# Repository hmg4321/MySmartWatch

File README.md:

WatchMe

My Personal SmartWatch

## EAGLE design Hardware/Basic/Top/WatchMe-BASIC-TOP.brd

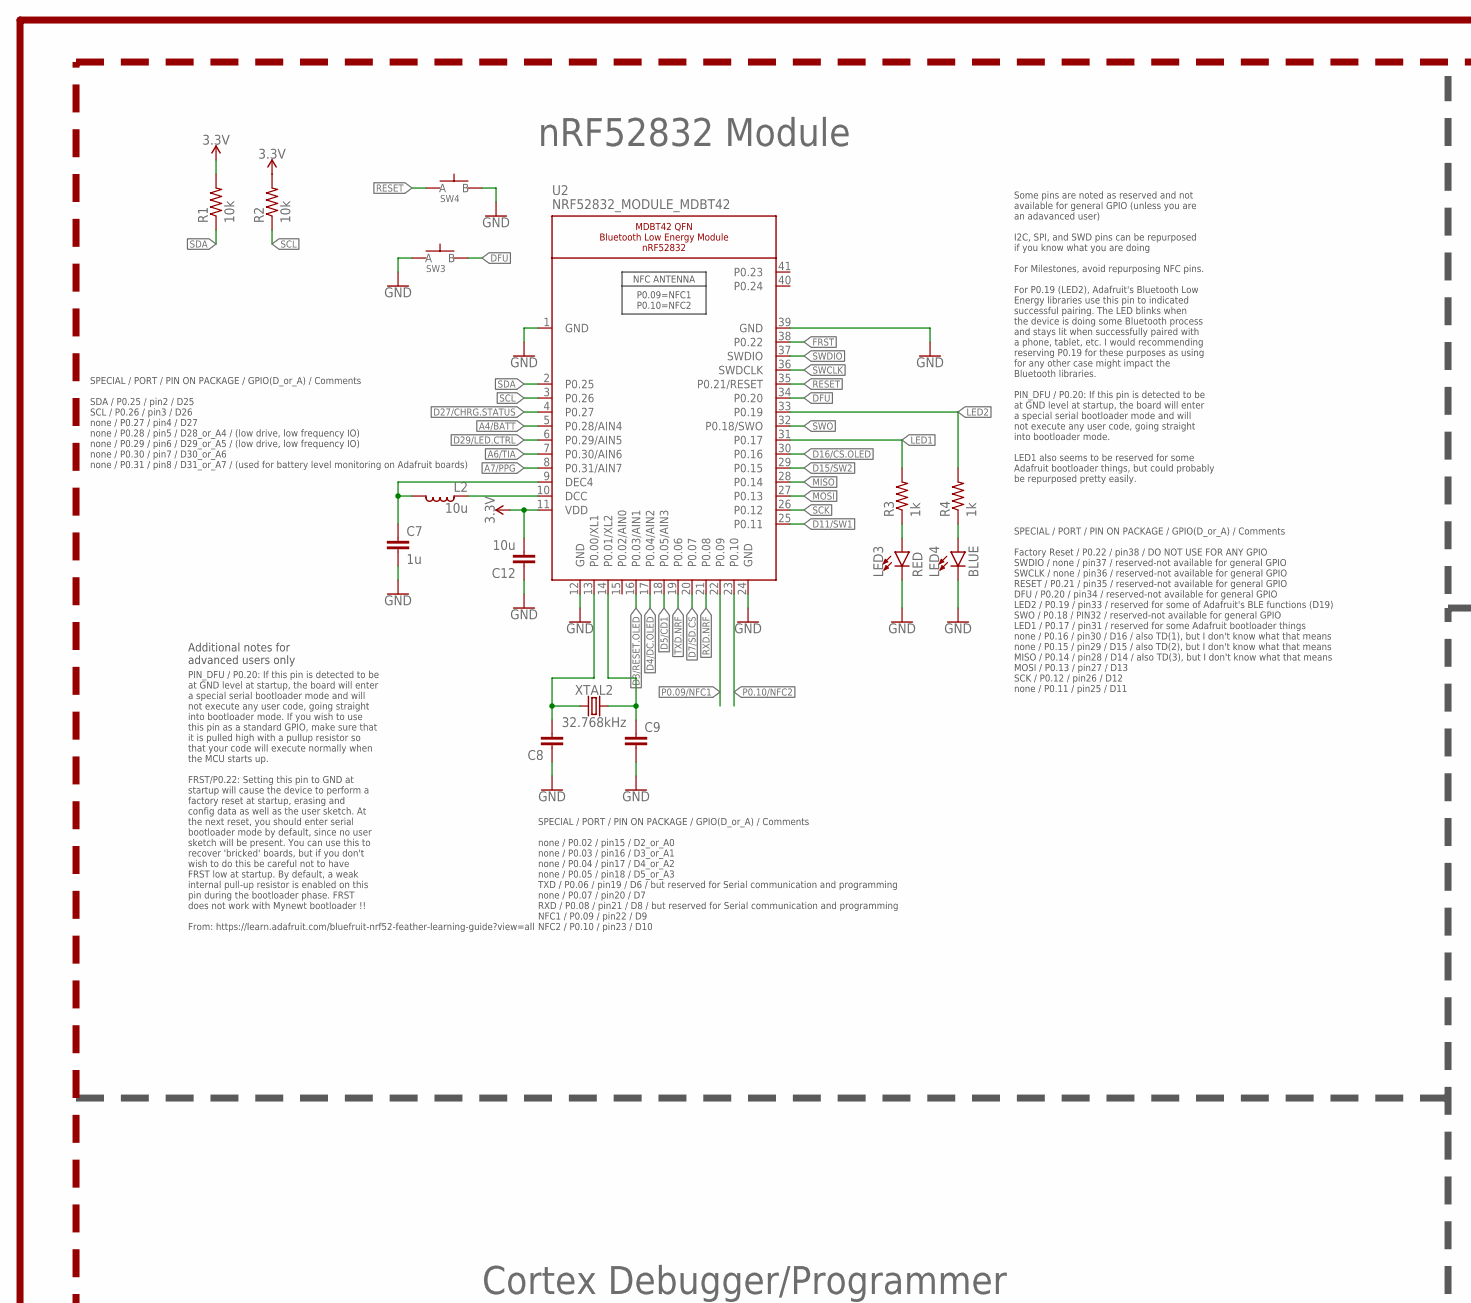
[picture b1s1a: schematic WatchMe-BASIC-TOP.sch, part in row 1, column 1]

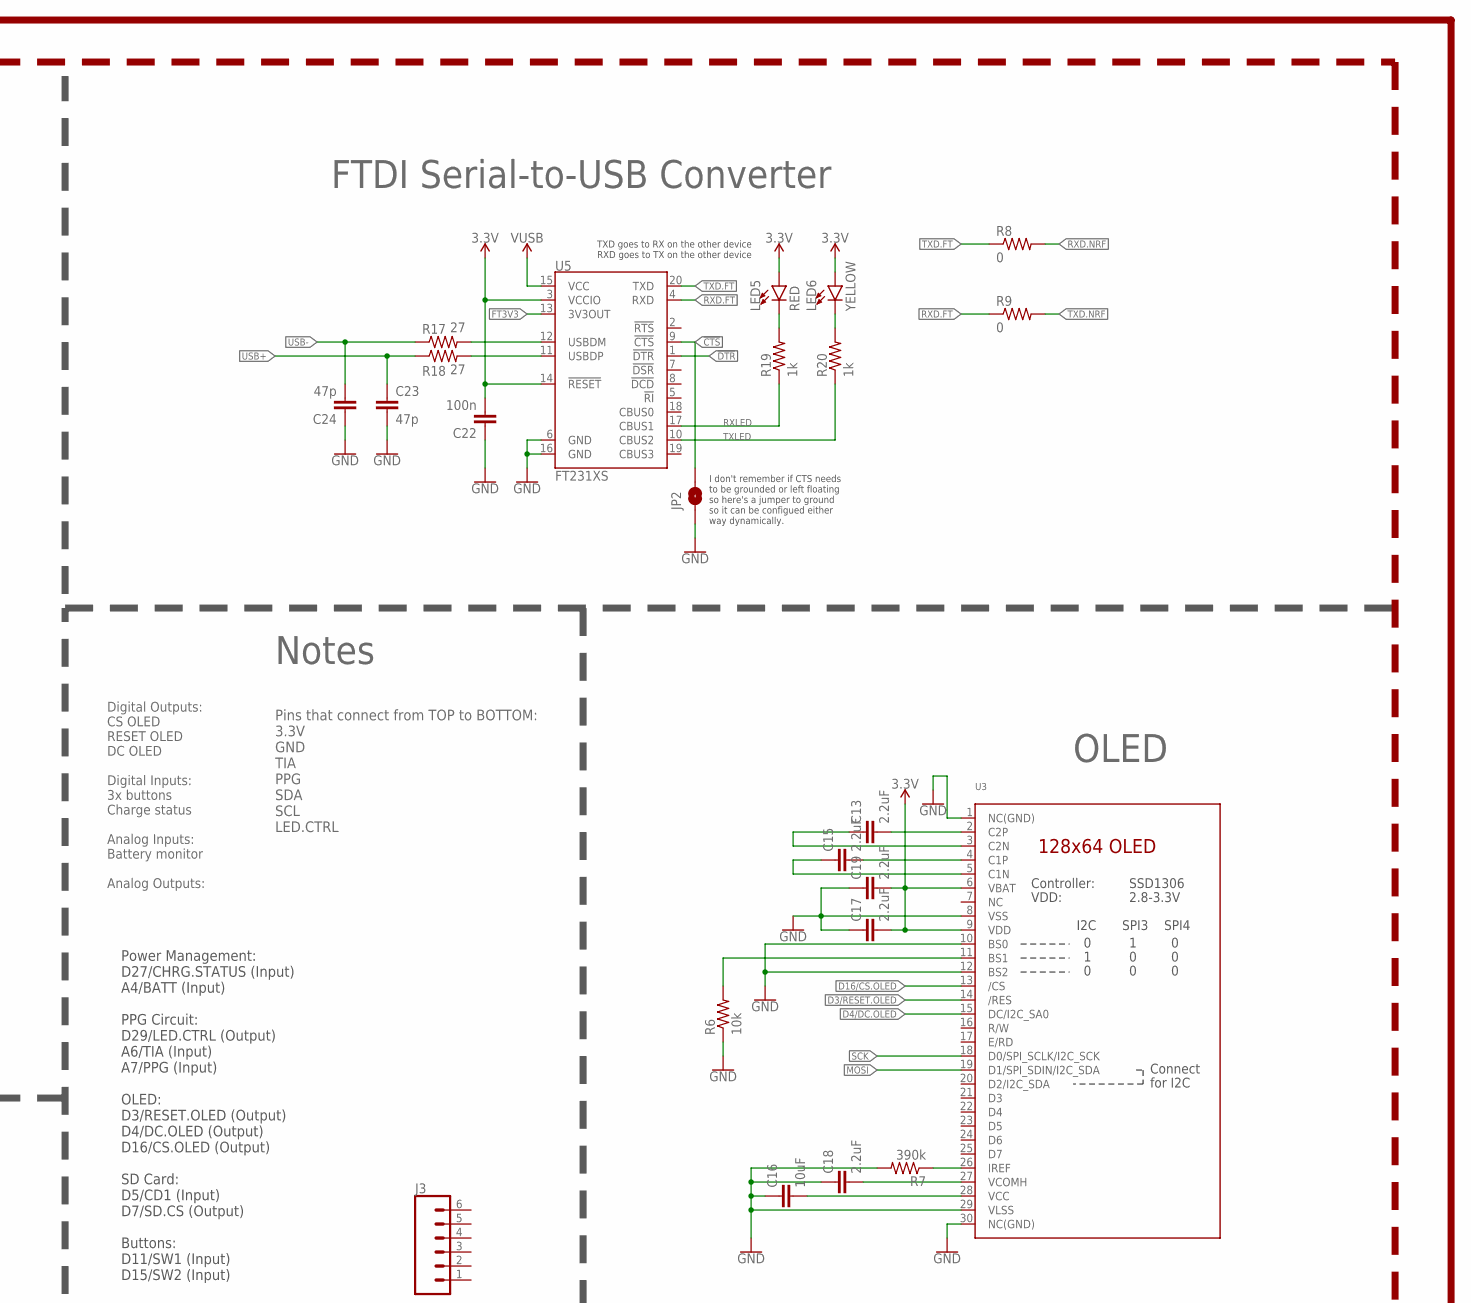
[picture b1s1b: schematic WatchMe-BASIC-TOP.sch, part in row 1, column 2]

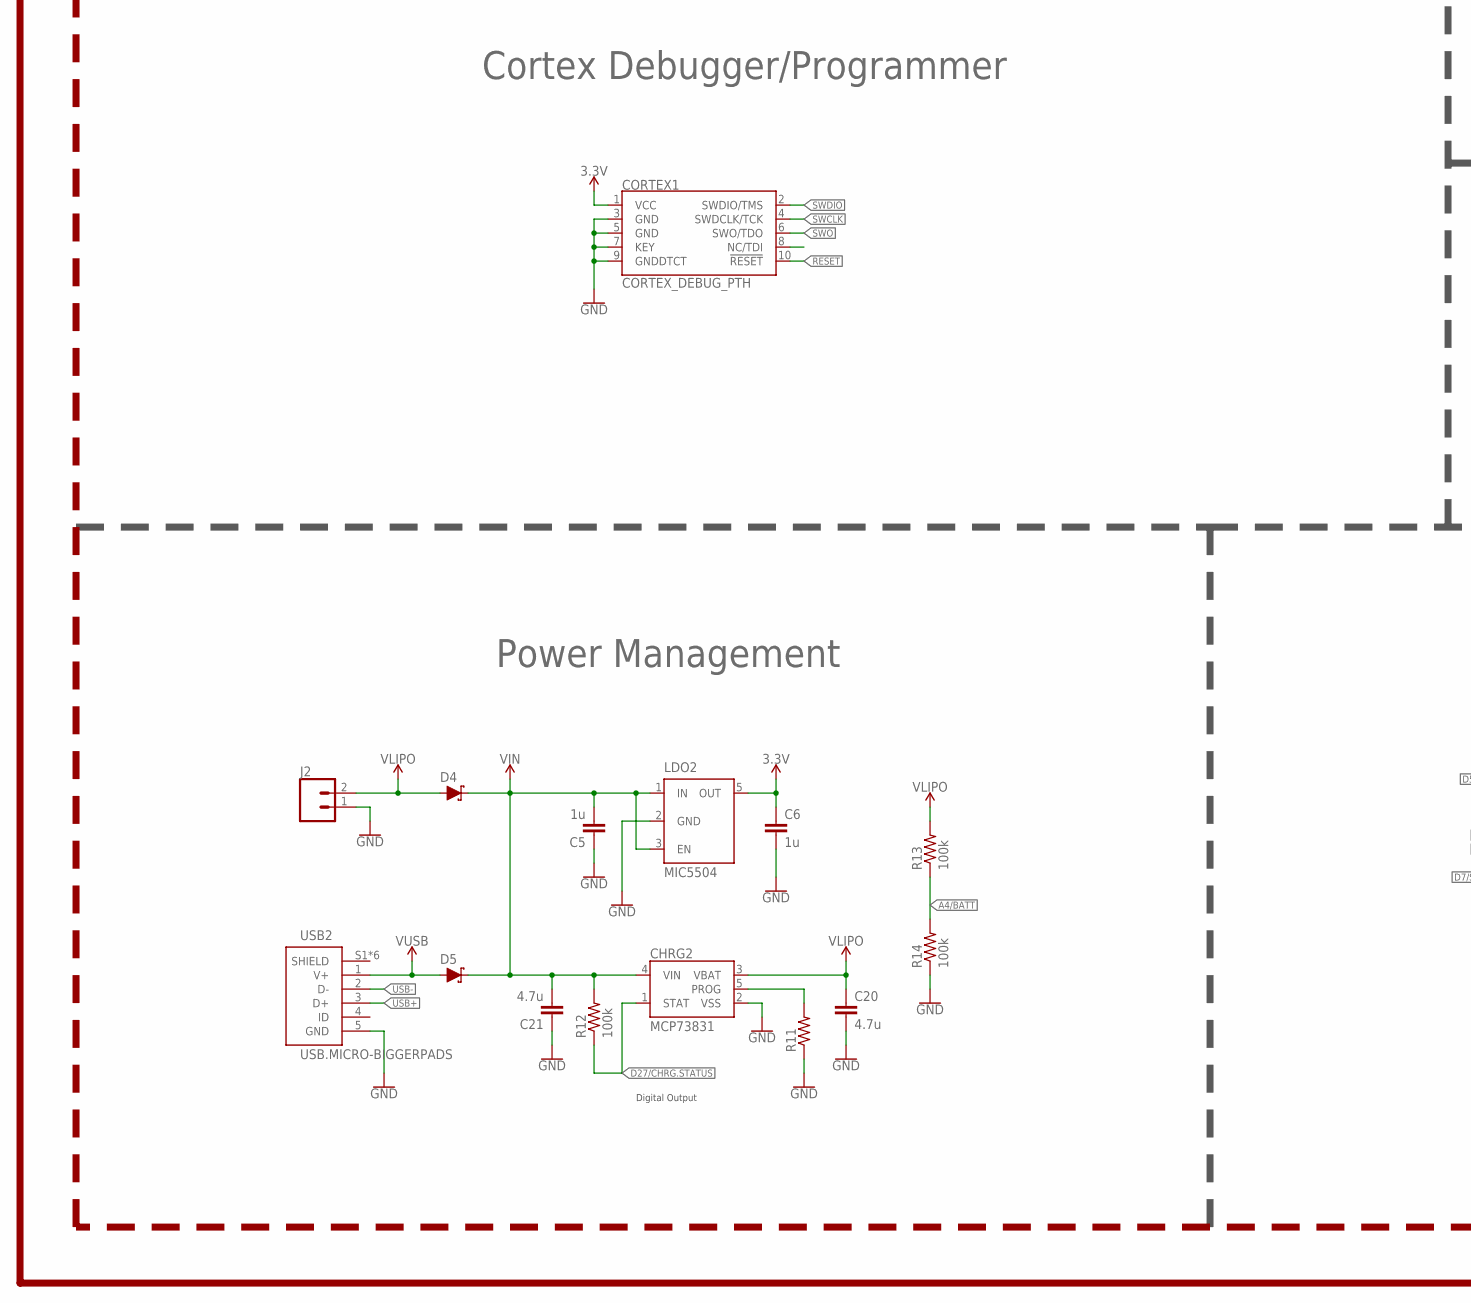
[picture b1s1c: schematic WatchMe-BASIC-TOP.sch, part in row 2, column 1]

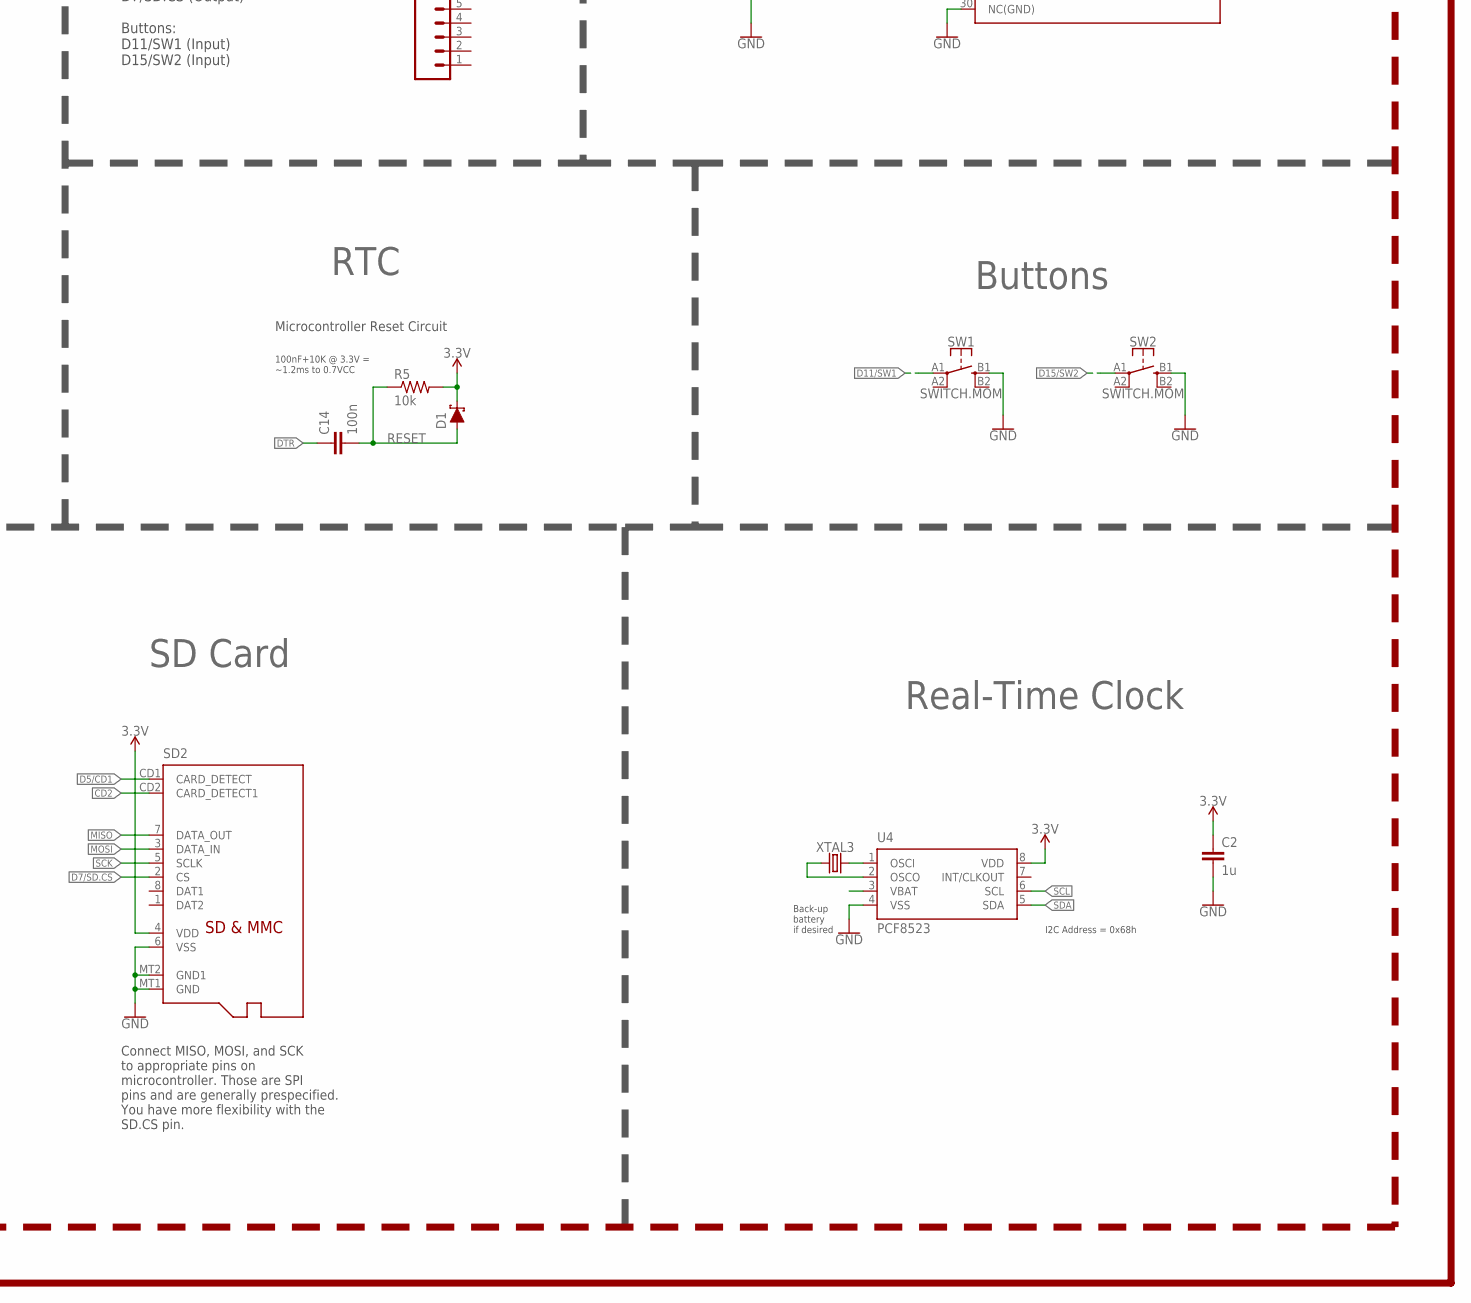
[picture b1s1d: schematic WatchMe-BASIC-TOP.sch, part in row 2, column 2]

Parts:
C2, C5, C6, C7: 1u; C0603
C8, C9: CAPACITOR0603; C0603
C12: 10u; C0805
C13, C15, C17, C18, C19: 2.2uF; C0402
C14, C22: 100n; C0603
C16: 10uF; C0603
C20, C21: 4.7u; C0603
C23, C24: 47p; C0603
CHRG2: MCP73831; SOT23-5
CORTEX1: CORTEX_DEBUG_PTH; 2X5-PTH-1.27MM
D1, D4, D5: SCHOTTKY-USC; USC
J2: CONN_02; 1X02
J3: CONN_061.27MM; 1X06_1.27MM
JP2: JUMPER-SMT_2_NO_SILK; SMT-JUMPER_2_NO_SILK
L2: 10u; L0603
LDO2: MIC5504; SOT23-5
LED3, LED5: RED; LED-0603
LED4: BLUE; LED-0603
LED6: YELLOW; LED-0603
R1, R2, R5, R6: 10k; R0603
R3, R4, R19, R20: 1k; R0603
R7: 390k; R0603
R8, R9: 0; R0603
R11: RESISTOR0603; R0603
R12, R13, R14: 100k; R0603
R17, R18: 27; R0603
SD2: MICROSD
SW1, SW2: SWITCH.MOM; TACTILE_SWITCH_SMD_6.2MM_TALL
SW3, SW4: SPST-PTS830GG140-COPY.1-3; BUTTON-GULLWING
U2: NRF52832_MODULE_MDBT42; BLE_MODULE_RAYTAC_MDBT42
U3: DISP_OLED_UG-2864HSWEG01-NO-WRAPAROUND; UG-2864HSWEG01_0.96IN_NO-WRAPAROUND
U4: PCF8523; SO8; DIGIKEY 568-5306-1-ND
U5: FT231XS; SSOP20_L
USB2: USB.MICRO-BIGGERPADS; USB-MICRO-01.BIGGERPADS
XTAL2: 32.768kHz; 2-SMD.NOLEAD.2.0MMTO1.2MM
XTAL3: 32.7680kHz; 2-SMD.NOLEAD.2.0MMTO1.2MM

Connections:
3.3V: C2.1, C6.1, C12.2, C17.2, C19.2, C22.2, CORTEX1.1 (VCC), D1.- (C), LDO2.5 (OUT), LED5.A, LED6.A, R1.2, R2.2, R5.2, SD2.4 (VDD), U2.11 (VDD), U3.6 (VBAT), U3.9 (VDD), U4.8 (VDD), U5.3 (VCCIO), U5.14 (!RESET)
!CTS: JP2.2, U5.9 (!CTS)
!DTR: U5.1 (!DTR)
A4/BATT: R13.1, R14.2, U2.5 (P0.28/AIN4)
A6/TIA: U2.7 (P0.30/AIN6)
A7/PPG: U2.8 (P0.31/AIN7)
CD2: SD2.CD2 (CARD_DETECT1)
D3/RESET.OLED: U2.16 (P0.03/AIN1), U3.14 (/RES)
D4/DC.OLED: U2.17 (P0.04/AIN2), U3.15 (DC/I2C_SA0)
D5/CD1: SD2.CD1 (CARD_DETECT), U2.18 (P0.05/AIN3)
D7/SD.CS: SD2.2 (CS), U2.20 (P0.07)
D11/SW1: SW1.A1 (1), U2.25 (P0.11)
D15/SW2: SW2.A1 (1), U2.29 (P0.15)
D16/CS.OLED: U2.30 (P0.16), U3.13 (/CS)
D27/CHRG.STATUS: CHRG2.1 (STAT), R12.1, U2.4 (P0.27)
D29/LED.CTRL: U2.6 (P0.29/AIN5)
DFU: SW3.3 (B), U2.34 (P0.20)
DTR: C14.1
FRST: U2.38 (P0.22)
FT3V3: U5.13 (3V3OUT)
GND: C2.2, C5.1, C6.2, C7.2, C8.1, C9.2, C12.1, C16.1, C17.1, C18.1, C19.1, C20.2, C21.1, C22.1, C23.2, C24.1, CHRG2.2 (VSS), CORTEX1.3 (GND), CORTEX1.5 (GND), CORTEX1.7 (KEY), CORTEX1.9 (GNDDTCT), J2.1, JP2.1, LDO2.2 (GND), LED3.C, LED4.C, R6.1, R7.2, R11.1, R14.1, SD2.6 (VSS), SD2.MT1 (GND), SD2.MT2 (GND1), SW1.B1 (3), SW2.B1 (3), SW3.1 (A), SW4.3 (B), U2.1 (GND), U2.12 (GND), U2.24 (GND), U2.39 (GND), U3.1 (NC(GND)), U3.8 (VSS), U3.10 (BS0), U3.12 (BS2), U3.29 (VLSS), U3.30 (NC(GND)), U4.4 (VSS), U5.6 (GND), U5.16 (GND), USB2.5 (GND)
LED1: R3.2, U2.31 (P0.17)
LED2: R4.2, U2.33 (P0.19)
MISO: SD2.7 (DATA_OUT), U2.28 (P0.14)
MOSI: SD2.3 (DATA_IN), U2.27 (P0.13), U3.19 (D1/SPI_SDIN/I2C_SDA)
unnamed: R6.2, U3.11 (BS1)
unnamed: R7.1, U3.26 (IREF)
unnamed: C13.2, U3.2 (C2P)
unnamed: C8.2, U2.13 (P0.00/XL1), XTAL2.P$1 (1)
unnamed: C13.1, U3.3 (C2N)
unnamed: C9.1, U2.14 (P0.01/XL2), XTAL2.P$2 (2)
unnamed: C15.2, U3.4 (C1P)
unnamed: C15.1, U3.5 (C1N)
unnamed: LED3.A, R3.1
unnamed: LED4.A, R4.1
unnamed: L2.1, U2.10 (DCC)
unnamed: C7.1, L2.2, U2.9 (DEC4)
unnamed: C16.2, U3.28 (VCC)
unnamed: C18.2, U3.27 (VCOMH)
unnamed: CHRG2.5 (PROG), R11.2
unnamed: U4.2 (OSCO), XTAL3.P$1 (1)
unnamed: U4.1 (OSCI), XTAL3.P$2 (2)
unnamed: R17.2, U5.12 (USBDM)
unnamed: R18.2, U5.11 (USBDP)
unnamed: LED5.C, R19.2
unnamed: LED6.C, R20.2
P0.09/NFC1: U2.22 (P0.09)
P0.10/NFC2: U2.23 (P0.10)
RESET: C14.2, CORTEX1.10 (!RESET), D1.+ (A), R5.1, SW4.1 (A), U2.35 (P0.21/RESET)
RXD.FT: R9.1, U5.4 (RXD)
RXD.NRF: R8.2, U2.21 (P0.08)
RXLED: R19.1, U5.17 (CBUS1)
SCK: SD2.5 (SCLK), U2.26 (P0.12), U3.18 (D0/SPI_SCLK/I2C_SCK)
SCL: R2.1, U2.3 (P0.26), U4.6 (SCL)
SDA: R1.1, U2.2 (P0.25), U4.5 (SDA)
SWCLK: CORTEX1.4 (SWDCLK/TCK), U2.36 (SWDCLK)
SWDIO: CORTEX1.2 (SWDIO/TMS), U2.37 (SWDIO)
SWO: CORTEX1.6 (SWO/TDO), U2.32 (P0.18/SWO)
TXD.FT: R8.1, U5.20 (TXD)
TXD.NRF: R9.2, U2.19 (P0.06)
TXLED: R20.1, U5.10 (CBUS2)
USB+: C23.1, R18.1, USB2.3 (D+)
USB-: C24.2, R17.1, USB2.2 (D-)
VBATT: U4.3 (VBAT)
VIN: C5.2, C21.2, CHRG2.4 (VIN), D4.- (C), D5.- (C), LDO2.1 (IN), LDO2.3 (EN), R12.2
VLIPO: C20.1, CHRG2.3 (VBAT), D4.+ (A), J2.2, R13.2
V_USB: D5.+ (A), U5.15 (VCC), USB2.1 (V+)

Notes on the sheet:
Microcontroller Reset Circuit
100nF+10K @ 3.3V = ~1.2ms to 0.7VCC
SPECIAL / PORT / PIN ON PACKAGE / GPIO(D_or_A) / Comments SDA / P0.25 / pin2 / D25 SCL / P0.26 / pin3 / D26 none / P0.27 / pin4 / D27 none / P0.28 / pin5 / D28_or_A4 / (low drive, low frequency IO) none / P0.29 / pin6 / D29_or_A5 / (low drive, low frequency IO) none / P0.30 / pin7 / D30_or_A6 none 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
SPECIAL / PORT / PIN ON PACKAGE / GPIO(D_or_A) / Comments none / P0.02 / pin15 / D2_or_A0 none / P0.03 / pin16 / D3_or_A1 none / P0.04 / pin17 / D4_or_A2 none / P0.05 / pin18 / D5_or_A3 TXD / P0.06 / pin19 / D6 / but reserved for Serial communication and programming none / P0.07 / pin20 / D7 RXD / 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
SPECIAL / PORT / PIN ON PACKAGE / GPIO(D_or_A) / Comments Factory Reset / P0.22 / pin38 / DO NOT USE FOR ANY GPIO SWDIO / none / pin37 / reserved-not available for general GPIO SWCLK / none / pin36 / reserved-not available for general GPIO RESET / P0.21 / pin35 / reserved-not available for general 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
Some pins are noted as reserved and not available for general GPIO (unless you are an adavanced user) I2C, SPI, and SWD pins can be repurposed if you know what you are doing For Milestones, avoid repurposing NFC pins. For P0.19 (LED2), Adafruit's Bluetooth Low Energy libraries use this pin to indic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
PIN_DFU / P0.20: If this pin is detected to be at GND level at startup, the board will enter a special serial bootloader mode and will not execute any user code, going straight into bootloader mode. If you wish to use this pin as a standard GPIO, make sure that it is pulled high with a pullup resis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
Additional notes for advanced users only
Connect MISO, MOSI, and SCK to appropriate pins on microcontroller. Those are SPI pins and are generally prespecified. You have more flexibility with the SD.CS pin.
I2C Address = 0x68h
Back-up battery if desired
nRF52832 Module
Power Management
SD Card
Buttons
Real-Time Clock
OLED
Cortex Debugger/Programmer
RTC
TXD goes to RX on the other device RXD goes to TX on the other device
I don't remember if CTS needs to be grounded or left floating so here's a jumper to ground so it can be configued either way dynamically.
FTDI Serial-to-USB Converter
Digital Outputs: CS OLED RESET OLED DC OLED Digital Inputs: 3x buttons Charge status Analog Inputs: Battery monitor Analog Outputs:
Notes
Pins that connect from TOP to BOTTOM: 3.3V GND TIA PPG SDA SCL LED.CTRL
Digital Output
Power Management: D27/CHRG.STATUS (Input) A4/BATT (Input) PPG Circuit: D29/LED.CTRL (Output) A6/TIA (Input) A7/PPG (Input) OLED: D3/RESET.OLED (Output) D4/DC.OLED (Output) D16/CS.OLED (Output) SD Card: D5/CD1 (Input) D7/SD.CS (Output) Buttons: D11/SW1 (Input) D15/SW2 (Input)

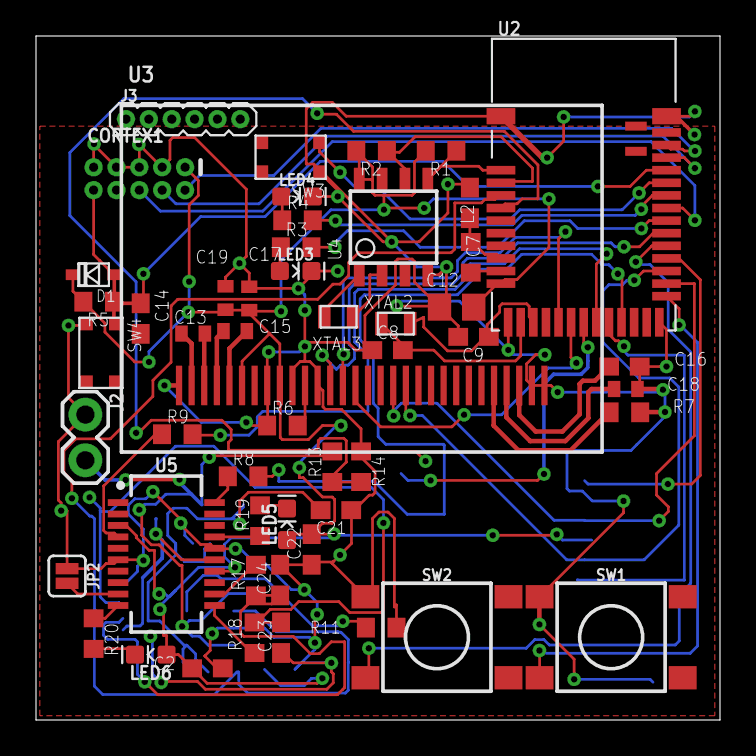
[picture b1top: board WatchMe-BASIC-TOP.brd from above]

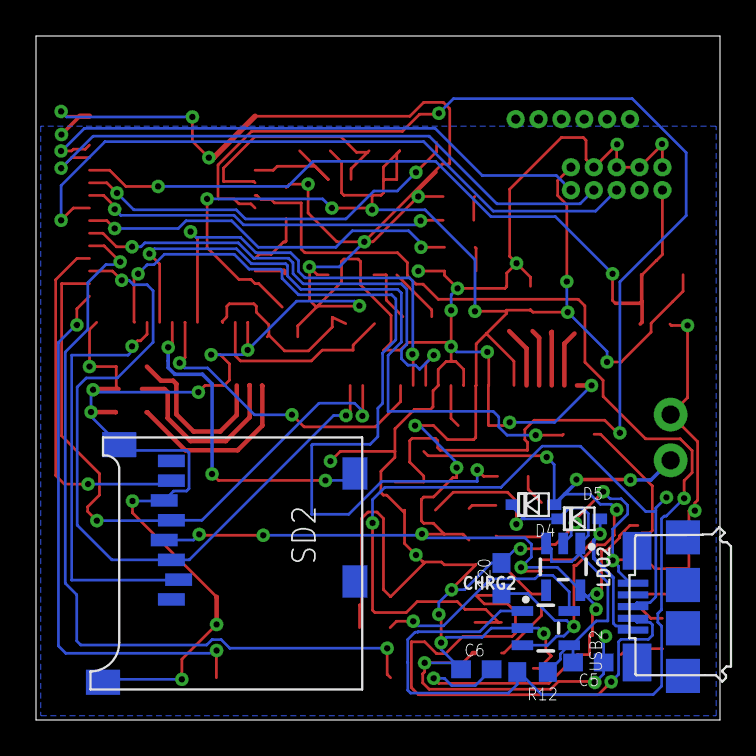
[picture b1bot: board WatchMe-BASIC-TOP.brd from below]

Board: 2 copper layers, 38.0 x 38.0 mm, 62 parts (10 on the bottom side), 56 nets.

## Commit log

2020-06-30 features list
2020-06-30 edited name and features of watch
2020-07-01 adding folder structures
2020-07-08 update 1
2020-07-09 updated top brd/sch
2020-07-14 updated top board/sch
2020-07-14 updated top board/sch again
2020-07-16 continuin top board work
2020-07-21 updated top board, still pretty chaotic
2020-07-21 top board routing complete
2020-07-21 Added LSM6DS3 sensor
2020-07-22 Beginning to resolve DRC errors
2020-07-22 removed LSM6DS3 sensor - already on bottom board
2020-07-28 fixed all DRC errors/warnings
2020-07-28 fixed remaining warnings
2020-07-29 updated bottom and PPG boards
2020-08-04 updated firmware
